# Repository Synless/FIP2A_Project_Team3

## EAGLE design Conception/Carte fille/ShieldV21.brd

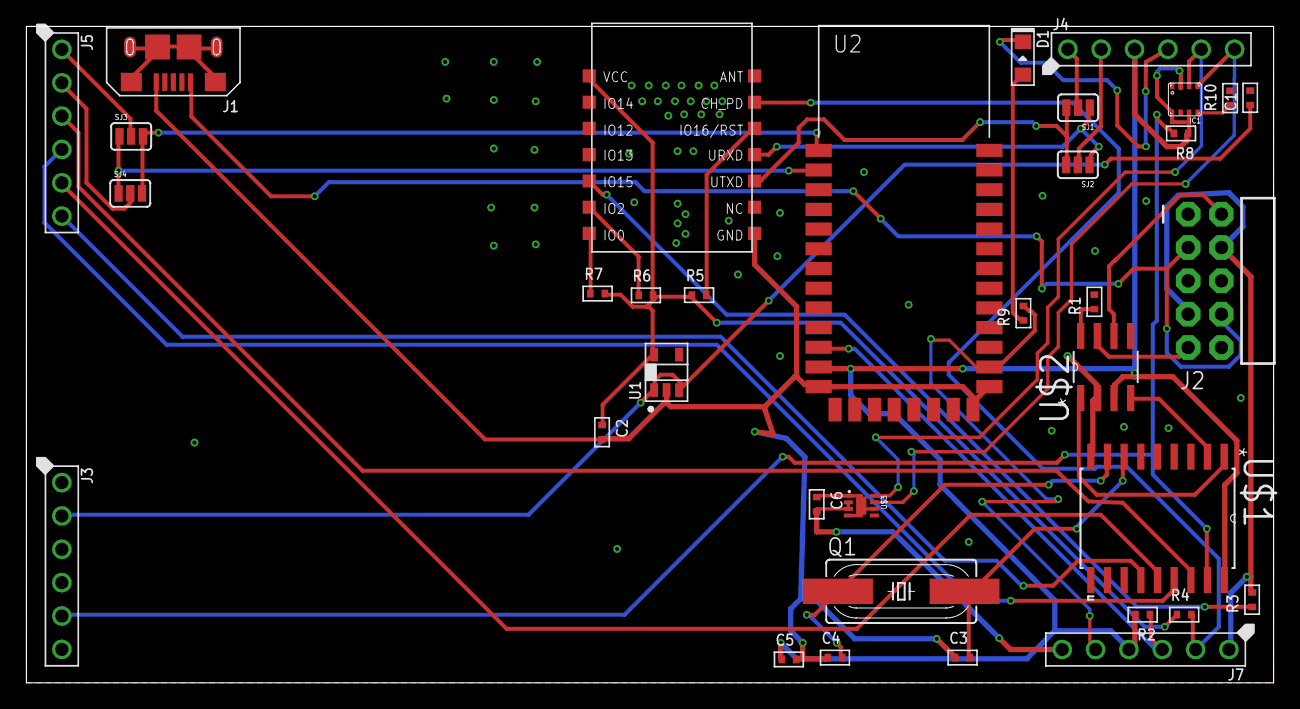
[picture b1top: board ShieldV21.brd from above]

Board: 2 copper layers, 95.0 x 50.0 mm, 35 parts (0 on the bottom side), 38 nets.

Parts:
C1, C2: 1uF 16V; C0402
C3, C4: 22pf; C0402
C5: 100nf; C0402
C6: 0.1uF; C0402
D1: LED0805
IC1: BME280
J1: MICROUSB-RIGHT
J2: 2X5-RA
J3, J4, J5, J7: PTH_2.54MM_01X06
Q1: HC49UP
R1: 17k; R0402
R2, R8, R10: 10k; R0402
R3, R5, R6, R7: 10K; R0402
R4: 2.2K; R0402
R9: 470; R0402
SJ1, SJ2, SJ3, SJ4: SJ_3
U1: TLV70233PDBVR; SOT-23-5
U2: HC_05; BLUETOOTH_SMD
U$1: MCP2515-I/SO; SOIC127P1034X264-18N
U$2: MCP2551-I/SN; SOIC127P600X175-8N
U$3: MAX17048DFN8; DFN-8
U$7: ESP-03_NO_SOLDER; ESP-03_NO_SOLDER_PASTE

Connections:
3.3V: C5.P$1, IC1.2, IC1.6, IC1.8, J4.P$3, J7.P$4, R2.P$2, R8.P$1, U2.12, U$1.18, U$2.3
3.3V_ESP: C2.P$1, R4.P$1, R5.P$1, R6.P$2, R7.P$2, U1.P$5, U$7.VCC
5V_IN: J1.1, J2.3, J2.8
BAT+: C6.P$2, J7.P$6, U$3.P$2, U$3.P$3
CANH: J2.9, U$2.7
CANRX: U$1.2, U$2.4
CANTX: U$1.1, U$2.1
GND: C1.P$2, C2.P$2, C3.P$1, C4.P$1, C5.P$2, C6.P$1, D1.CATHODE, IC1.1, IC1.7, J1.5, J2.4, J2.7, J4.P$4, J7.P$1, R1.P$2, R3.P$2, R10.P$2, U1.P$2, U2.13, U2.21, U2.22, U$1.9, U$2.2, U$3.P$1, U$3.P$4, U$3.P$6, U$3.P$9, U$7.GND
LED_HC05: J7.P$5, R9.P$2, U2.23
MISO: J5.P$4, U$1.15
MOSI: J5.P$5, U$1.14
unnamed: D1.ANODE, R9.P$1
unnamed: C3.P$2, Q1.2, U$1.7
unnamed: C4.P$2, Q1.1, U$1.8
unnamed: J2.2, U$2.6
unnamed: R1.P$1, U$2.8
unnamed: R5.P$2, U$7.GPIO16/RST
unnamed: IC1.5, R10.P$1
unnamed: R7.P$1, U$7.GPIO0
unnamed: R6.P$1, U$7.GPIO2
unnamed: R3.P$1, U$7.GPIO15
PA07_GPIO1: J7.P$2, R4.P$2, U$7.CH_PD
PA21_GPIO0: J5.P$3, U$1.16
PB22_TXD_GPIO3: J4.P$1, SJ1.2
PB23_RXD_GPIO4: J4.P$2, SJ2.2
RST_CAN: J3.P$5, R8.P$2, U$1.17
RST_HC05: J7.P$3, R2.P$1, U2.11
RX_HC05: SJ3.1, SJ4.1, U2.2
RX_WIFI: SJ1.3, SJ2.3, U$7.UTXD
SCK: J5.P$6, U$1.13
SCL: IC1.4, J4.P$6, U$3.P$7
SDA: IC1.3, J4.P$5, U$3.P$8
SERIAL1_RX: J5.P$1, SJ3.2
SERIAL1_TX: J5.P$2, SJ4.2
SLD: J1.S1, J1.S2, J1.S3, J1.S4, J1.S5, J1.S6
S_POWER: C1.P$1, J3.P$2, U1.P$1, U1.P$3
TX_HC05: SJ3.3, SJ4.3, U2.1
TX_WIFI: SJ1.1, SJ2.1, U$7.URXD

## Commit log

2016-04-25 Test unitaires bluetooth / CAN
2016-04-25 Test unitaire wifi WIP
2016-04-25 Add library (console toolkit)
2016-04-25 wifi update
2016-04-25 update wifi
2016-04-25 Bluetooth update 1
2016-04-25 Baudrate to 115200
2016-04-25 Fix missing baudrate
2016-04-26 add sprite management, add integration of CAN and BT
2016-04-27 Bluetooth integration complete
2016-05-06 pre release
2016-05-06 Synless sprite editor
2016-05-06 BT_Master true robot simulator message
2016-05-07 Final release
2016-05-09 Final release : add licence to specifics files
2016-05-10 Update Form1.cs
    Mise à l’échelle adaptative et non plus fixe.
2016-05-10 Update Form1.cs
    Mise à l'échelle adaptative et non plus fixe.

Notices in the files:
parts and their libraries:
SparkFun-Connectors: Licensing: Creative Commons ShareAlike 4.0 International - https://creativecommons.org/licenses/by-sa/4.0
